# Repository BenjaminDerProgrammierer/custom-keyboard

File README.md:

# Custom keyboard

My try on a custom keyboard. I've always wanted to design a bigger PCB and case, and Keeb was the perfect opportunity. My challenge is a near-ISO keyboard layout.

## TODO

* what you built, why, and what you learned
* Add Rotary Encoder and OLED display ("Extras")

## Attribution

Thanks to [Hack Club Keeb](https://keeb.hackclub.com/) for encouraging me to build my own keyboard.

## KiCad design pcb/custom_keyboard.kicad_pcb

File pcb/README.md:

# KiCAD project directory

## Adding gerbers

* Go to File → Fabrication Outputs → Gerbers (.gbr)
* Select all layers (F.Cu, B.Cu, F.Silkscreen, B.Silkscreen, F.Mask, B.Mask, Edge.Cuts) and click Plot
* Then click Generate Drill Files to export the .drl file
* Zip the output folder and commit it alongside your .kicad_pcb and .kicad_sch files

## Layout

For viewing the source layout, upload `layout.json` to <https://www.keyboard-layout-editor.com/>

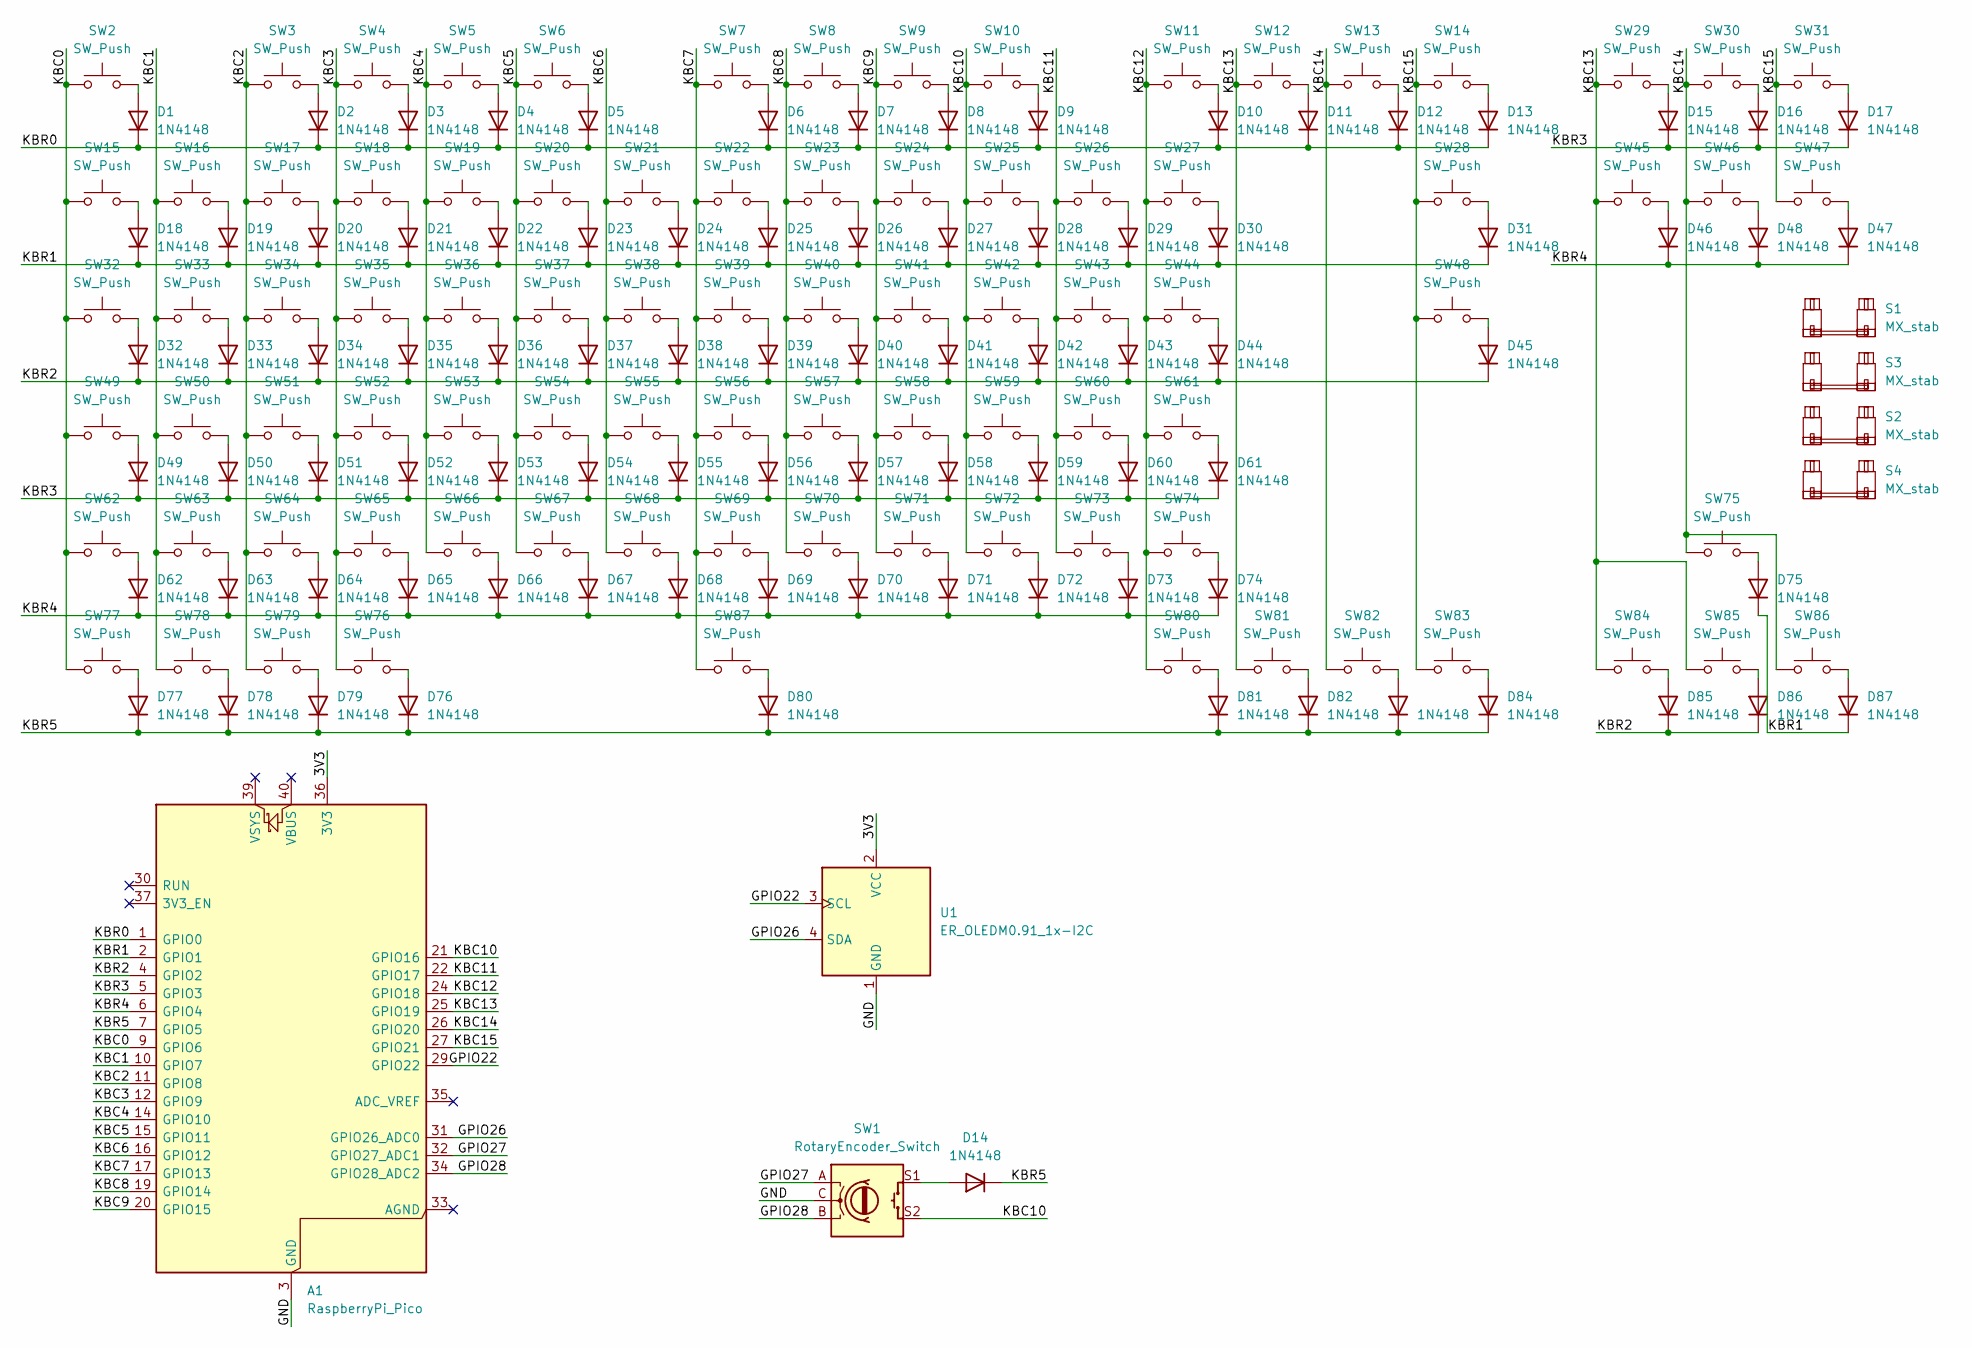
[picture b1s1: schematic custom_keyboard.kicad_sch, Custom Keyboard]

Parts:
A1: RaspberryPi_Pico; RaspberryPi_Pico_SMD
D1, D2, D3, D4, D5, D6, D7, D8, D9, D10, D11, D12, D13, D14, D15, D16, D17, D18, D19, D20, D21, D22, D23, D24, D25, D26, D27, D28, D29, D30, D31, D32, D33, D34, D35, D36, D37, D38, D39, D40, D41, D42, D43, D44, D45, D46, D47, D48, D49, D50, D51, D52, D53, D54, D55, D56, D57, D58, D59, D60, D61, D62, D63, D64, D65, D66, D67, D68, D69, D70, D71, D72, D73, D74, D75, D76, D77, D78, D79, D80, D81, D82, D83, D84, D85, D86, D87: 1N4148; D_DO-35_SOD27_P7.62mm_Horizontal
S1: MX_stab; STAB_MX_2u
S2: MX_stab; STAB_MX_ISO
S3: MX_stab; STAB_MX_2.75u
S4: MX_stab; STAB_MX_5u
SW1: RotaryEncoder_Switch; RotaryEncoder_Alps_EC11E-Switch_Vertical_H20mm
SW2, SW3, SW4, SW5, SW6, SW7, SW8, SW9, SW10, SW11, SW12, SW13, SW14, SW15, SW16, SW17, SW18, SW19, SW20, SW21, SW22, SW23, SW24, SW25, SW26, SW27, SW28, SW29, SW30, SW31, SW33, SW34, SW35, SW36, SW37, SW38, SW39, SW40, SW41, SW42, SW43, SW44, SW45, SW46, SW47, SW48, SW50, SW51, SW52, SW53, SW54, SW55, SW56, SW57, SW58, SW59, SW60, SW61, SW63, SW64, SW65, SW66, SW67, SW68, SW69, SW70, SW71, SW72, SW73, SW74, SW75, SW84, SW85, SW86, SW87: SW_Push; SW_MX_1u
SW32: SW_Push; SW_MX_1.5u
SW49: SW_Push; SW_MX_1.75u
SW62, SW76, SW77, SW78, SW79, SW80, SW81, SW82, SW83: SW_Push; SW_MX_1.25u
U1: ER_OLEDM0.91_1x-I2C

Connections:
/3V3: A1.36 (3V3), U1.2 (VCC)
/GND: A1.3 (GND), A1.8 (GND), A1.13 (GND), A1.18 (GND), A1.23 (GND), A1.28 (GND), A1.38 (GND), SW1.C, U1.1 (GND)
/GPIO22: A1.29 (GPIO22), U1.3 (SCL)
/GPIO26: A1.31 (GPIO26_ADC0), U1.4 (SDA)
/GPIO27: A1.32 (GPIO27_ADC1), SW1.A
/GPIO28: A1.34 (GPIO28_ADC2), SW1.B
/KBC0: A1.9 (GPIO6), SW2.1, SW15.1, SW32.1, SW49.1, SW62.1, SW77.1
/KBC1: A1.10 (GPIO7), SW16.1, SW33.1, SW50.1, SW63.1, SW78.1
/KBC2: A1.11 (GPIO8), SW3.1, SW17.1, SW34.1, SW51.1, SW64.1, SW79.1
/KBC3: A1.12 (GPIO9), SW4.1, SW18.1, SW35.1, SW52.1, SW65.1, SW76.1
/KBC4: A1.14 (GPIO10), SW5.1, SW19.1, SW36.1, SW53.1, SW66.1
/KBC5: A1.15 (GPIO11), SW6.1, SW20.1, SW37.1, SW54.1, SW67.1
/KBC6: A1.16 (GPIO12), SW21.1, SW38.1, SW55.1, SW68.1
/KBC7: A1.17 (GPIO13), SW7.1, SW22.1, SW39.1, SW56.1, SW69.1, SW87.1
/KBC8: A1.19 (GPIO14), SW8.1, SW23.1, SW40.1, SW57.1, SW70.1
/KBC9: A1.20 (GPIO15), SW9.1, SW24.1, SW41.1, SW58.1, SW71.1
/KBC10: A1.21 (GPIO16), SW1.S2, SW10.1, SW25.1, SW42.1, SW59.1, SW72.1
/KBC11: A1.22 (GPIO17), SW26.1, SW43.1, SW60.1, SW73.1
/KBC12: A1.24 (GPIO18), SW11.1, SW27.1, SW44.1, SW61.1, SW74.1, SW80.1
/KBC13: A1.25 (GPIO19), SW12.1, SW29.1, SW45.1, SW81.1, SW84.1, SW85.1
/KBC14: A1.26 (GPIO20), SW13.1, SW30.1, SW46.1, SW75.1, SW82.1, SW86.1
/KBC15: A1.27 (GPIO21), SW14.1, SW28.1, SW31.1, SW47.1, SW48.1, SW83.1
/KBR0: A1.1 (GPIO0), D1.1 (K), D2.1 (K), D3.1 (K), D4.1 (K), D5.1 (K), D6.1 (K), D7.1 (K), D8.1 (K), D9.1 (K), D10.1 (K), D11.1 (K), D12.1 (K), D13.1 (K)
/KBR1: A1.2 (GPIO1), D18.1 (K), D19.1 (K), D20.1 (K), D21.1 (K), D22.1 (K), D23.1 (K), D24.1 (K), D25.1 (K), D26.1 (K), D27.1 (K), D28.1 (K), D29.1 (K), D30.1 (K), D31.1 (K), D75.1 (K), D87.1 (K)
/KBR2: A1.4 (GPIO2), D32.1 (K), D33.1 (K), D34.1 (K), D35.1 (K), D36.1 (K), D37.1 (K), D38.1 (K), D39.1 (K), D40.1 (K), D41.1 (K), D42.1 (K), D43.1 (K), D44.1 (K), D45.1 (K), D85.1 (K), D86.1 (K)
/KBR3: A1.5 (GPIO3), D15.1 (K), D16.1 (K), D17.1 (K), D49.1 (K), D50.1 (K), D51.1 (K), D52.1 (K), D53.1 (K), D54.1 (K), D55.1 (K), D56.1 (K), D57.1 (K), D58.1 (K), D59.1 (K), D60.1 (K), D61.1 (K)
/KBR4: A1.6 (GPIO4), D46.1 (K), D47.1 (K), D48.1 (K), D62.1 (K), D63.1 (K), D64.1 (K), D65.1 (K), D66.1 (K), D67.1 (K), D68.1 (K), D69.1 (K), D70.1 (K), D71.1 (K), D72.1 (K), D73.1 (K), D74.1 (K)
/KBR5: A1.7 (GPIO5), D14.1 (K), D76.1 (K), D77.1 (K), D78.1 (K), D79.1 (K), D80.1 (K), D81.1 (K), D82.1 (K), D83.1 (K), D84.1 (K)
unnamed: D1.2 (A), SW2.2
unnamed: D2.2 (A), SW3.2
unnamed: D3.2 (A), SW4.2
unnamed: D4.2 (A), SW5.2
unnamed: D5.2 (A), SW6.2
unnamed: D6.2 (A), SW7.2
unnamed: D7.2 (A), SW8.2
unnamed: D8.2 (A), SW9.2
unnamed: D9.2 (A), SW10.2
unnamed: D10.2 (A), SW11.2
unnamed: D11.2 (A), SW12.2
unnamed: D12.2 (A), SW13.2
unnamed: D13.2 (A), SW14.2
unnamed: D14.2 (A), SW1.S1
unnamed: D15.2 (A), SW29.2
unnamed: D16.2 (A), SW30.2
unnamed: D17.2 (A), SW31.2
unnamed: D18.2 (A), SW15.2
unnamed: D19.2 (A), SW16.2
unnamed: D20.2 (A), SW17.2
unnamed: D21.2 (A), SW18.2
unnamed: D22.2 (A), SW19.2
unnamed: D23.2 (A), SW20.2
unnamed: D24.2 (A), SW21.2
unnamed: D25.2 (A), SW22.2
unnamed: D26.2 (A), SW23.2
unnamed: D27.2 (A), SW24.2
unnamed: D28.2 (A), SW25.2
unnamed: D29.2 (A), SW26.2
unnamed: D30.2 (A), SW27.2
unnamed: D31.2 (A), SW28.2
unnamed: D32.2 (A), SW32.2
unnamed: D33.2 (A), SW33.2
unnamed: D34.2 (A), SW34.2
unnamed: D35.2 (A), SW35.2
unnamed: D36.2 (A), SW36.2
unnamed: D37.2 (A), SW37.2
unnamed: D38.2 (A), SW38.2
unnamed: D39.2 (A), SW39.2
unnamed: D40.2 (A), SW40.2
unnamed: D41.2 (A), SW41.2
unnamed: D42.2 (A), SW42.2
unnamed: D43.2 (A), SW43.2
unnamed: D44.2 (A), SW44.2
unnamed: D45.2 (A), SW48.2
unnamed: D46.2 (A), SW45.2
unnamed: D47.2 (A), SW47.2
unnamed: D48.2 (A), SW46.2
unnamed: D49.2 (A), SW49.2
unnamed: D50.2 (A), SW50.2
unnamed: D51.2 (A), SW51.2
unnamed: D52.2 (A), SW52.2
unnamed: D53.2 (A), SW53.2
unnamed: D54.2 (A), SW54.2
unnamed: D55.2 (A), SW55.2
unnamed: D56.2 (A), SW56.2
unnamed: D57.2 (A), SW57.2
unnamed: D58.2 (A), SW58.2
unnamed: D59.2 (A), SW59.2
unnamed: D60.2 (A), SW60.2
unnamed: D61.2 (A), SW61.2
unnamed: D62.2 (A), SW62.2
unnamed: D63.2 (A), SW63.2
unnamed: D64.2 (A), SW64.2
unnamed: D65.2 (A), SW65.2
unnamed: D66.2 (A), SW66.2
unnamed: D67.2 (A), SW67.2
unnamed: D68.2 (A), SW68.2
unnamed: D69.2 (A), SW69.2
unnamed: D70.2 (A), SW70.2
unnamed: D71.2 (A), SW71.2
unnamed: D72.2 (A), SW72.2
unnamed: D73.2 (A), SW73.2
unnamed: D74.2 (A), SW74.2
unnamed: D75.2 (A), SW75.2
unnamed: D76.2 (A), SW76.2
unnamed: D77.2 (A), SW77.2
unnamed: D78.2 (A), SW78.2
unnamed: D79.2 (A), SW79.2
unnamed: D80.2 (A), SW87.2
unnamed: D81.2 (A), SW80.2
unnamed: D82.2 (A), SW81.2
unnamed: D83.2 (A), SW82.2
unnamed: D84.2 (A), SW83.2
unnamed: D85.2 (A), SW84.2
unnamed: D86.2 (A), SW85.2
unnamed: D87.2 (A), SW86.2

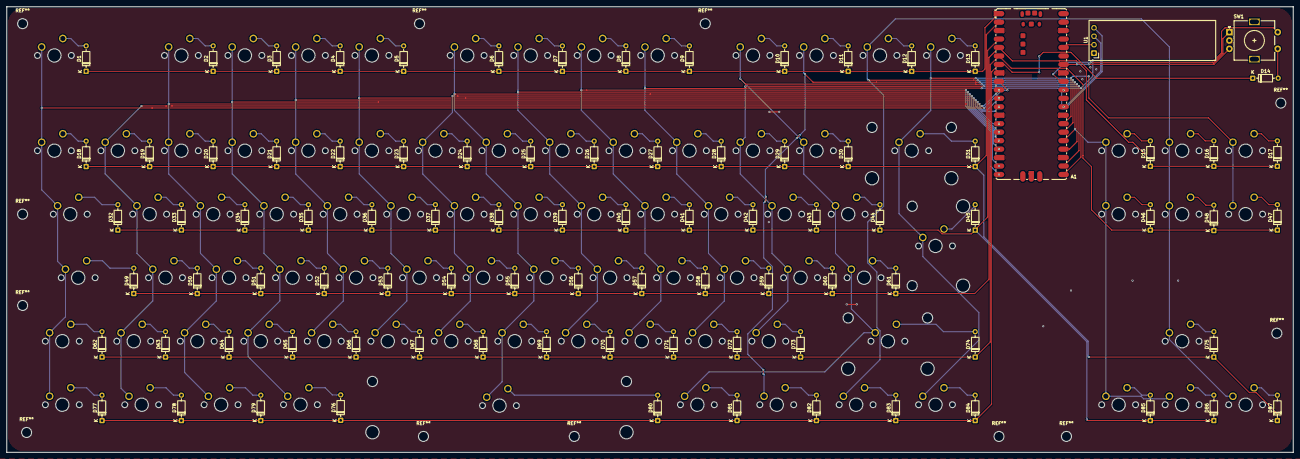
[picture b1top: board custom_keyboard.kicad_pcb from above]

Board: 2 copper layers, 385.9 x 133.7 mm, 180 parts (0 on the bottom side), 115 nets.

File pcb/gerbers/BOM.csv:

"Id";"Designator";"Footprint";"Quantity";"Designation";"Supplier and ref";
1;"A1";"RaspberryPi_Pico_Common_SMD";1;"RaspberryPi_Pico";;;
2;"D1, D2, D3, D4, D5, D6, D7, D8, D9, D10, D11, D12, D13, D14, D15, D16, D17, D18, D19, D20, D21, D22, D23, D24, D25, D26, D27, D28, D29, D30, D31, D32, D33, D34, D35, D36, D37, D38, D39, D40, D41, D42, D43, D44, D45, D46, D47, D48, D49, D50, D51, D52, D53, D54, D55, D56, D57, D58, D59, D60, D61, D62, D63, D64, D65, D66, D67, D68, D69, D70, D71, D72, D73, D74, D75, D76, D77, D78, D79, D80, D81, D82, D83, D84, D85";"D_DO-35_SOD27_P7.62mm_Horizontal";85;"1N4148";;;
3;"S1";"STAB_MX_2u";1;"MX_stab";;;
4;"S2";"STAB_MX_ISO";1;"MX_stab";;;
5;"S3";"STAB_MX_2.75u";1;"MX_stab";;;
6;"S4";"STAB_MX_6.25u";1;"MX_stab";;;
7;"SW1, SW2, SW3, SW4, SW5, SW6, SW7, SW8, SW9, SW10, SW11, SW12, SW13, SW14, SW15, SW16, SW17, SW18, SW19, SW20, SW21, SW22, SW23, SW24, SW25, SW26, SW27, SW28, SW29, SW30, SW31, SW32, SW33, SW35, SW36, SW37, SW38, SW39, SW40, SW41, SW42, SW43, SW44, SW45, SW46, SW47, SW49, SW50, SW51, SW52, SW53, SW54, SW55, SW56, SW57, SW58, SW59, SW60, SW62, SW63, SW64, SW65, SW66, SW67, SW68, SW69, SW70, SW71, SW72, SW73, SW74, SW78, SW83, SW84, SW85";"SW_MX_1u";75;"SW_Push";;;
8;"SW34";"SW_MX_1.5u";1;"SW_Push";;;
9;"SW48";"SW_MX_1.75u";1;"SW_Push";;;
10;"SW61, SW75, SW76, SW77, SW79, SW80, SW81, SW82";"SW_MX_1.25u";8;"SW_Push";;;
